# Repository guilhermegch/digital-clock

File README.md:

# Digital clock #

This is a crystal based clock is made using only common ICs: 
- Binary Counter (CD4020, CD4017, 74HC393)
- AND gates (74HC08)
- NAND gates (CD4093)
- Multiplexer (74HC251)
- 7 segments display decoder (CD4511)

## How it works ##

This clock source is on a 32.768 kHz crystal. The signal is amplified by the NAND gates and sent to a frequency divider. Since 32786 = 2^15, we use the CD4020 14 stages with the output cascaded to a CD4017, so we have a stable 1 Hz oscillator. 

The 2048 Hz (Q3) and the 64 Hz (Q8) clocks are used by the fast and slow clock adjusts. Send the three signals into a multiplexer, and the clock signal goes to the 74HC393 counter that, combined with AND gates, makes the logic circuit. 

In the end, the counter stage numbers feed a binary to seven segment display decoder.

The seconds are counted in binary by the LEDs. Above the displays is the decimal. The displays show the hours in the 24h format, the Brazilian standard.

The PCB size is 100 x 100 mm, to feat on the promotional range of Chinese manufactures, like [PCBWay](https://www.pcbway.com) and [JLCPCB](https://jlcpcb.com).

Feel free to change the project to meet your needs.

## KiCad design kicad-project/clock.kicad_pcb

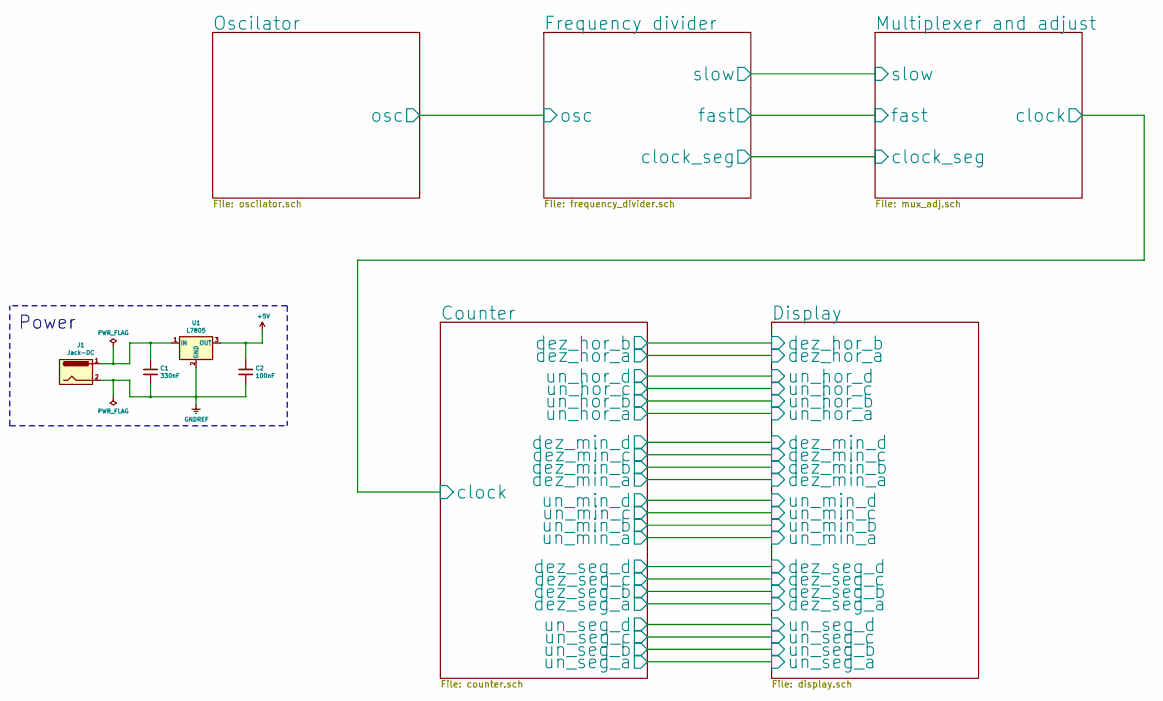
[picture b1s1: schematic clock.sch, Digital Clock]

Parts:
C1: 330nF; C_Rect_L7.0mm_W2.5mm_P5.00mm
C2: 100nF; C_Disc_D9.0mm_W5.0mm_P7.50mm
J1: Jack-DC; BarrelJack_Horizontal
U1: L7805; TO-220-3_Vertical

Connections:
+5V: C2.1, U1.3 (OUT); also elsewhere on the board
GNDREF: C1.2, C2.2, J1.2, U1.2 (GND); also elsewhere on the board
unnamed: C1.1, J1.1, U1.1 (IN)

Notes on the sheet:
Power

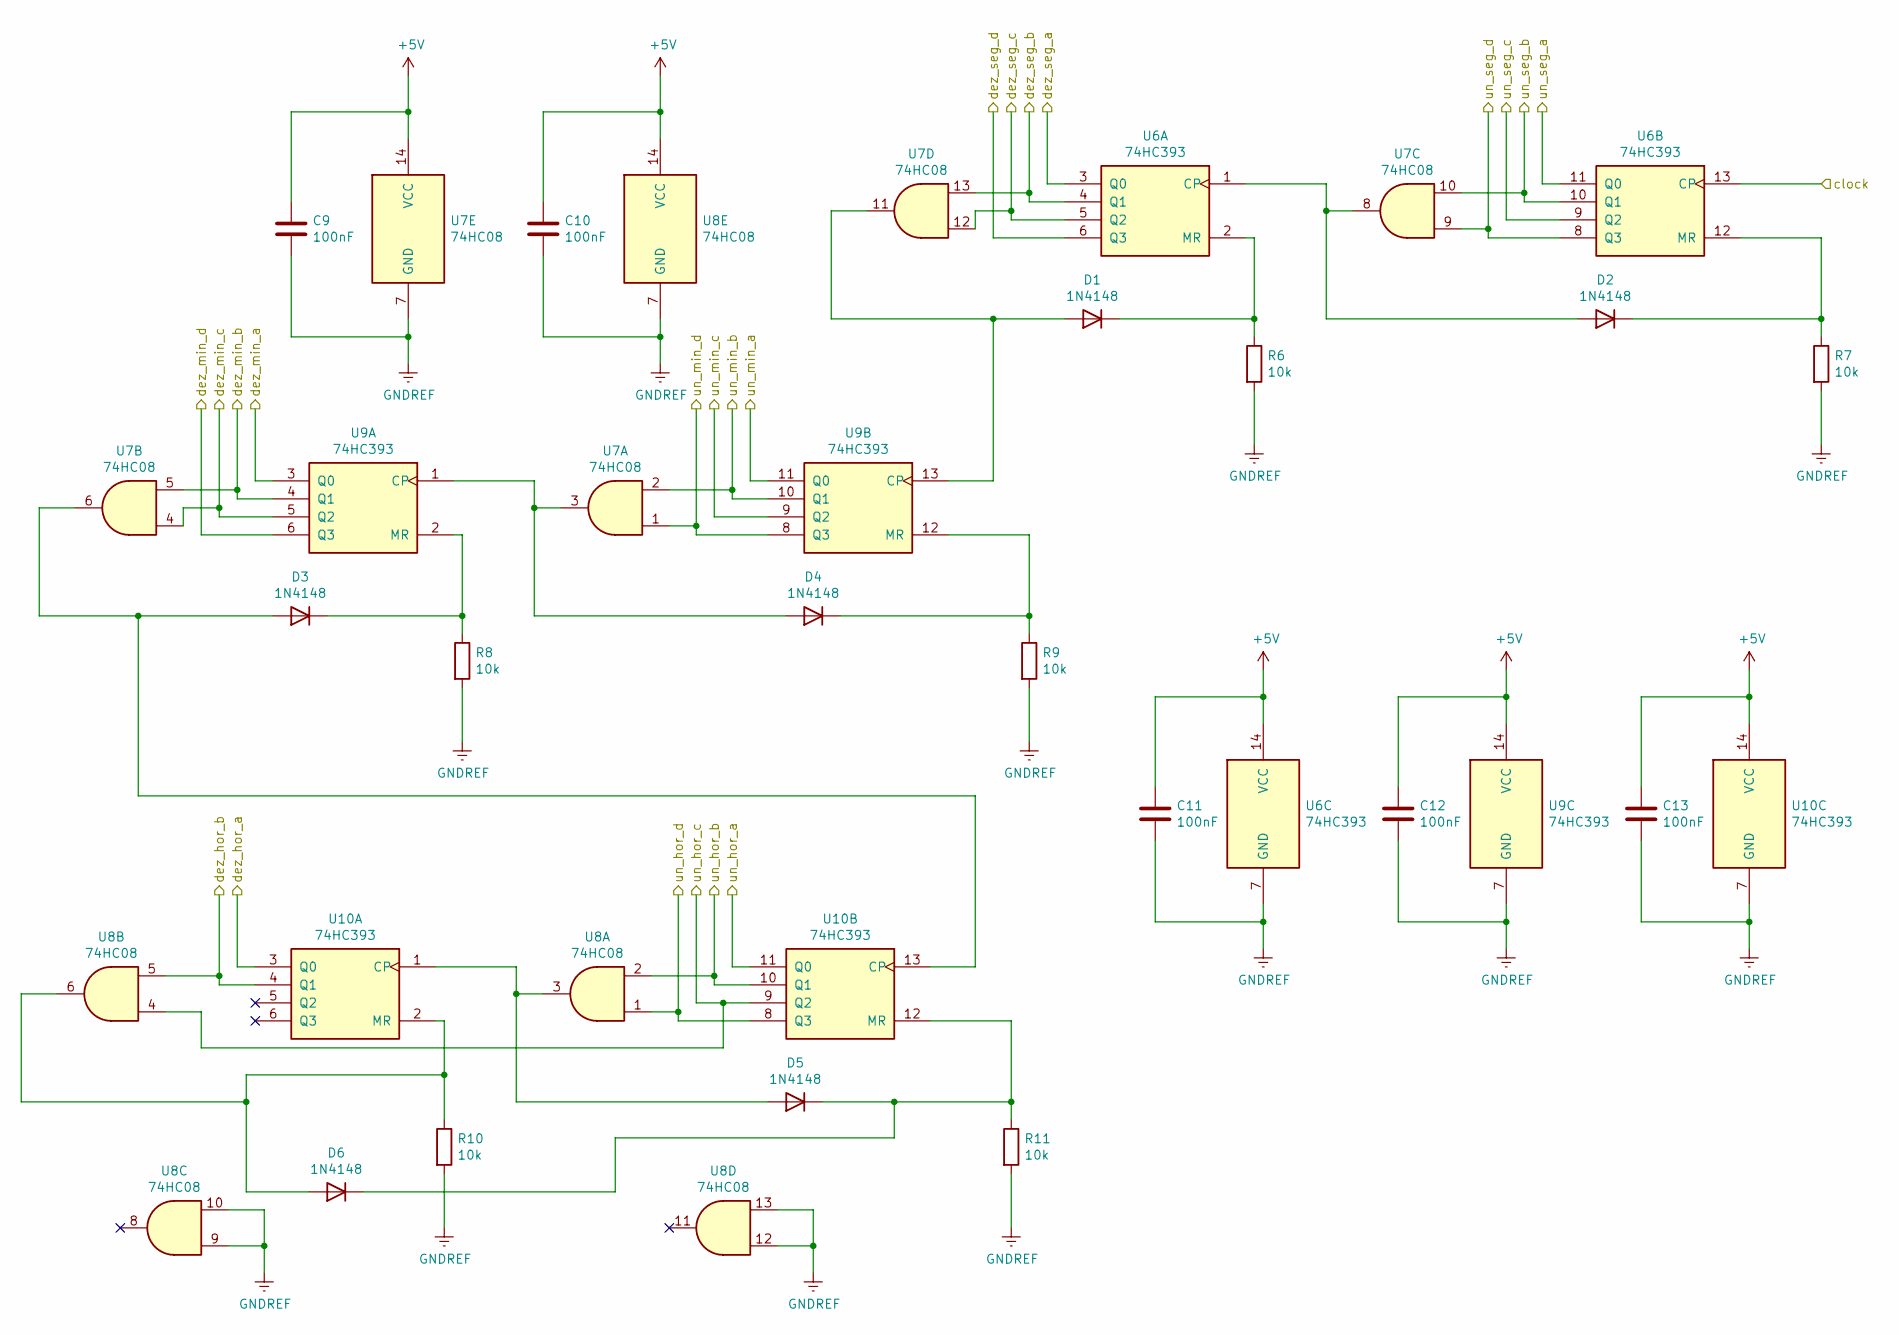
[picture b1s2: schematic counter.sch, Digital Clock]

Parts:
C9, C10, C11, C12, C13: 100nF; C_Disc_D9.0mm_W5.0mm_P7.50mm
D1, D2, D3, D4, D5, D6: 1N4148; D_DO-35_SOD27_P7.62mm_Horizontal
R6, R7, R8, R9, R10, R11: 10k; R_Axial_DIN0204_L3.6mm_D1.6mm_P7.62mm_Horizontal
U6, U9, U10: 74HC393; DIP-14_W7.62mm_Socket_LongPads
U7, U8: 74HC08; DIP-14_W7.62mm_Socket_LongPads

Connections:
+5V: C9.1, C10.1, C11.1, C12.1, C13.1, U6.14 (VCC), U7.14 (VCC), U8.14 (VCC), U9.14 (VCC), U10.14 (VCC); also elsewhere on the board
/Contador/clock: U6.13 (CP); also elsewhere on the board
/Contador/dez_hor_a: U10.3 (Q0); also elsewhere on the board
/Contador/dez_hor_b: U8.5, U10.4 (Q1); also elsewhere on the board
/Contador/dez_min_a: U9.3 (Q0); also elsewhere on the board
/Contador/dez_min_b: U7.5, U9.4 (Q1); also elsewhere on the board
/Contador/dez_min_c: U7.4, U9.5 (Q2); also elsewhere on the board
/Contador/dez_min_d: U9.6 (Q3); also elsewhere on the board
/Contador/dez_seg_a: U6.3 (Q0); also elsewhere on the board
/Contador/dez_seg_b: U6.4 (Q1), U7.13; also elsewhere on the board
/Contador/dez_seg_c: U6.5 (Q2), U7.12; also elsewhere on the board
/Contador/dez_seg_d: U6.6 (Q3); also elsewhere on the board
/Contador/un_hor_a: U10.11 (Q0); also elsewhere on the board
/Contador/un_hor_b: U8.2, U10.10 (Q1); also elsewhere on the board
/Contador/un_hor_c: U8.4, U10.9 (Q2); also elsewhere on the board
/Contador/un_hor_d: U8.1, U10.8 (Q3); also elsewhere on the board
/Contador/un_min_a: U9.11 (Q0); also elsewhere on the board
/Contador/un_min_b: U7.2, U9.10 (Q1); also elsewhere on the board
/Contador/un_min_c: U9.9 (Q2); also elsewhere on the board
/Contador/un_min_d: U7.1, U9.8 (Q3); also elsewhere on the board
/Contador/un_seg_a: U6.11 (Q0); also elsewhere on the board
/Contador/un_seg_b: U6.10 (Q1), U7.10; also elsewhere on the board
/Contador/un_seg_c: U6.9 (Q2); also elsewhere on the board
/Contador/un_seg_d: U6.8 (Q3), U7.9; also elsewhere on the board
GNDREF: C9.2, C10.2, C11.2, C12.2, C13.2, R6.2, R7.2, R8.2, R9.2, R10.2, R11.2, U6.7 (GND), U7.7 (GND), U8.7 (GND), U8.9, U8.10, U8.12, U8.13, U9.7 (GND), U10.7 (GND); also elsewhere on the board
unnamed: D1.1 (K), R6.1, U6.2 (MR)
unnamed: D1.2 (A), U7.11, U9.13 (CP)
unnamed: D2.1 (K), R7.1, U6.12 (MR)
unnamed: D2.2 (A), U6.1 (CP), U7.8
unnamed: D3.1 (K), R8.1, U9.2 (MR)
unnamed: D3.2 (A), U7.6, U10.13 (CP)
unnamed: D4.1 (K), R9.1, U9.12 (MR)
unnamed: D4.2 (A), U7.3, U9.1 (CP)
unnamed: D5.1 (K), D6.1 (K), R11.1, U10.12 (MR)
unnamed: D5.2 (A), U8.3, U10.1 (CP)
unnamed: D6.2 (A), R10.1, U8.6, U10.2 (MR)

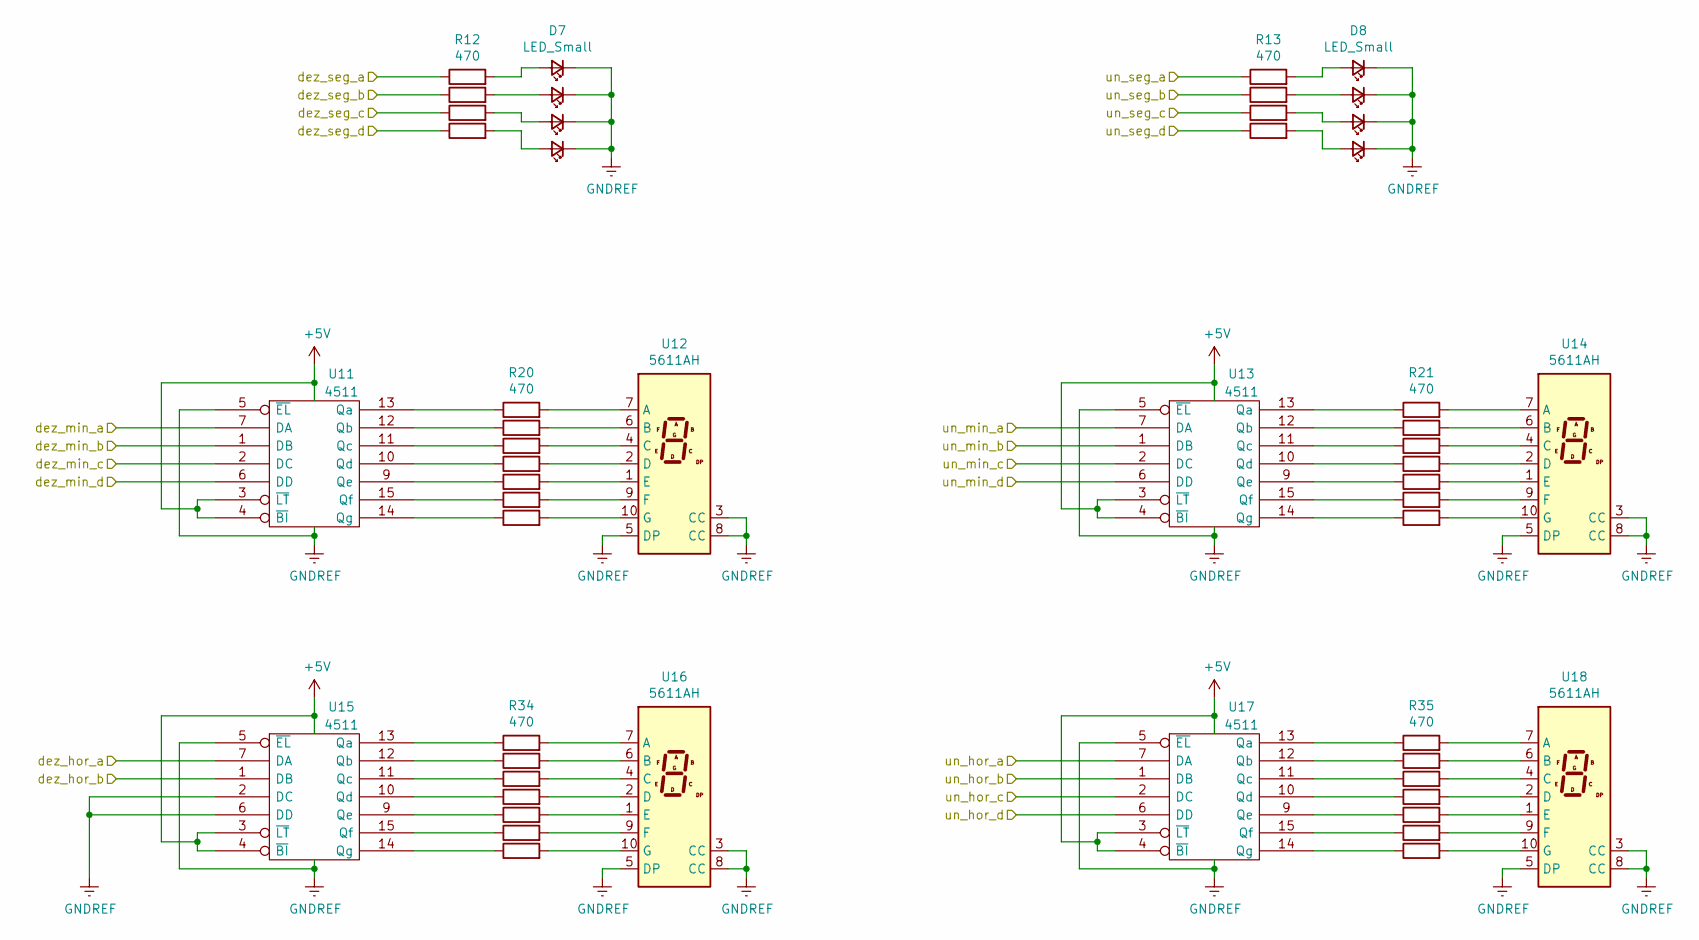
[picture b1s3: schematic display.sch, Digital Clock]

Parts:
D7, D8, D9, D10, D11, D12, D13, D14: LED_Small; LED_D5.0mm
R12, R13, R14, R15, R16, R17, R18, R19, R20, R21, R22, R23, R24, R25, R26, R27, R28, R29, R30, R31, R32, R33, R34, R35, R36, R37, R38, R39, R40, R41, R42, R43, R44, R45, R46, R47: 470; R_Axial_DIN0204_L3.6mm_D1.6mm_P7.62mm_Horizontal
U11, U13, U15, U17: 4511; DIP-16_W7.62mm_Socket_LongPads
U12, U14, U16, U18: 5611AH; D1X8K

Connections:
+5V: U11.3 (~LT), U11.4 (~BI), U11.16 (Vdd), U13.3 (~LT), U13.4 (~BI), U13.16 (Vdd), U15.3 (~LT), U15.4 (~BI), U15.16 (Vdd), U17.3 (~LT), U17.4 (~BI), U17.16 (Vdd); also elsewhere on the board
/Contador/dez_hor_a: U15.7 (DA); also elsewhere on the board
/Contador/dez_hor_b: U15.1 (DB); also elsewhere on the board
/Contador/dez_min_a: U11.7 (DA); also elsewhere on the board
/Contador/dez_min_b: U11.1 (DB); also elsewhere on the board
/Contador/dez_min_c: U11.2 (DC); also elsewhere on the board
/Contador/dez_min_d: U11.6 (DD); also elsewhere on the board
/Contador/dez_seg_a: R12.1; also elsewhere on the board
/Contador/dez_seg_b: R14.1; also elsewhere on the board
/Contador/dez_seg_c: R16.1; also elsewhere on the board
/Contador/dez_seg_d: R18.1; also elsewhere on the board
/Contador/un_hor_a: U17.7 (DA); also elsewhere on the board
/Contador/un_hor_b: U17.1 (DB); also elsewhere on the board
/Contador/un_hor_c: U17.2 (DC); also elsewhere on the board
/Contador/un_hor_d: U17.6 (DD); also elsewhere on the board
/Contador/un_min_a: U13.7 (DA); also elsewhere on the board
/Contador/un_min_b: U13.1 (DB); also elsewhere on the board
/Contador/un_min_c: U13.2 (DC); also elsewhere on the board
/Contador/un_min_d: U13.6 (DD); also elsewhere on the board
/Contador/un_seg_a: R13.1; also elsewhere on the board
/Contador/un_seg_b: R15.1; also elsewhere on the board
/Contador/un_seg_c: R17.1; also elsewhere on the board
/Contador/un_seg_d: R19.1; also elsewhere on the board
GNDREF: D7.1 (K), D8.1 (K), D9.1 (K), D10.1 (K), D11.1 (K), D12.1 (K), D13.1 (K), D14.1 (K), U11.5 (~EL), U11.8 (Vss), U12.3 (CC), U12.5 (DP), U12.8 (CC), U13.5 (~EL), U13.8 (Vss), U14.3 (CC), U14.5 (DP), U14.8 (CC), U15.2 (DC), U15.5 (~EL), U15.6 (DD), U15.8 (Vss), U16.3 (CC), U16.5 (DP), U16.8 (CC), U17.5 (~EL), U17.8 (Vss), U18.3 (CC), U18.5 (DP), U18.8 (CC); also elsewhere on the board
unnamed: D7.2 (A), R12.2
unnamed: D8.2 (A), R13.2
unnamed: D9.2 (A), R14.2
unnamed: D10.2 (A), R15.2
unnamed: D11.2 (A), R16.2
unnamed: D12.2 (A), R17.2
unnamed: D13.2 (A), R18.2
unnamed: D14.2 (A), R19.2
unnamed: R20.1, U11.13 (Qa)
unnamed: R20.2, U12.7 (A)
unnamed: R21.1, U13.13 (Qa)
unnamed: R21.2, U14.7 (A)
unnamed: R22.1, U11.12 (Qb)
unnamed: R22.2, U12.6 (B)
unnamed: R23.1, U13.12 (Qb)
unnamed: R23.2, U14.6 (B)
unnamed: R24.1, U11.11 (Qc)
unnamed: R24.2, U12.4 (C)
unnamed: R25.1, U13.11 (Qc)
unnamed: R25.2, U14.4 (C)
unnamed: R26.1, U11.10 (Qd)
unnamed: R26.2, U12.2 (D)
unnamed: R27.1, U13.10 (Qd)
unnamed: R27.2, U14.2 (D)
unnamed: R28.1, U11.9 (Qe)
unnamed: R28.2, U12.1 (E)
unnamed: R29.1, U13.9 (Qe)
unnamed: R29.2, U14.1 (E)
unnamed: R30.1, U11.15 (Qf)
unnamed: R30.2, U12.9 (F)
unnamed: R31.1, U13.15 (Qf)
unnamed: R31.2, U14.9 (F)
unnamed: R32.1, U11.14 (Qg)
unnamed: R32.2, U12.10 (G)
unnamed: R33.1, U13.14 (Qg)
unnamed: R33.2, U14.10 (G)
unnamed: R34.1, U15.13 (Qa)
unnamed: R34.2, U16.7 (A)
unnamed: R35.1, U17.13 (Qa)
unnamed: R35.2, U18.7 (A)
unnamed: R36.1, U15.12 (Qb)
unnamed: R36.2, U16.6 (B)
unnamed: R37.1, U17.12 (Qb)
unnamed: R37.2, U18.6 (B)
unnamed: R38.1, U15.11 (Qc)
unnamed: R38.2, U16.4 (C)
unnamed: R39.1, U17.11 (Qc)
unnamed: R39.2, U18.4 (C)
unnamed: R40.1, U15.10 (Qd)
unnamed: R40.2, U16.2 (D)
unnamed: R41.1, U17.10 (Qd)
unnamed: R41.2, U18.2 (D)
unnamed: R42.1, U15.9 (Qe)
unnamed: R42.2, U16.1 (E)
unnamed: R43.1, U17.9 (Qe)
unnamed: R43.2, U18.1 (E)
unnamed: R44.1, U15.15 (Qf)
unnamed: R44.2, U16.9 (F)
unnamed: R45.1, U17.15 (Qf)
unnamed: R45.2, U18.9 (F)
unnamed: R46.1, U15.14 (Qg)
unnamed: R46.2, U16.10 (G)
unnamed: R47.1, U17.14 (Qg)
unnamed: R47.2, U18.10 (G)

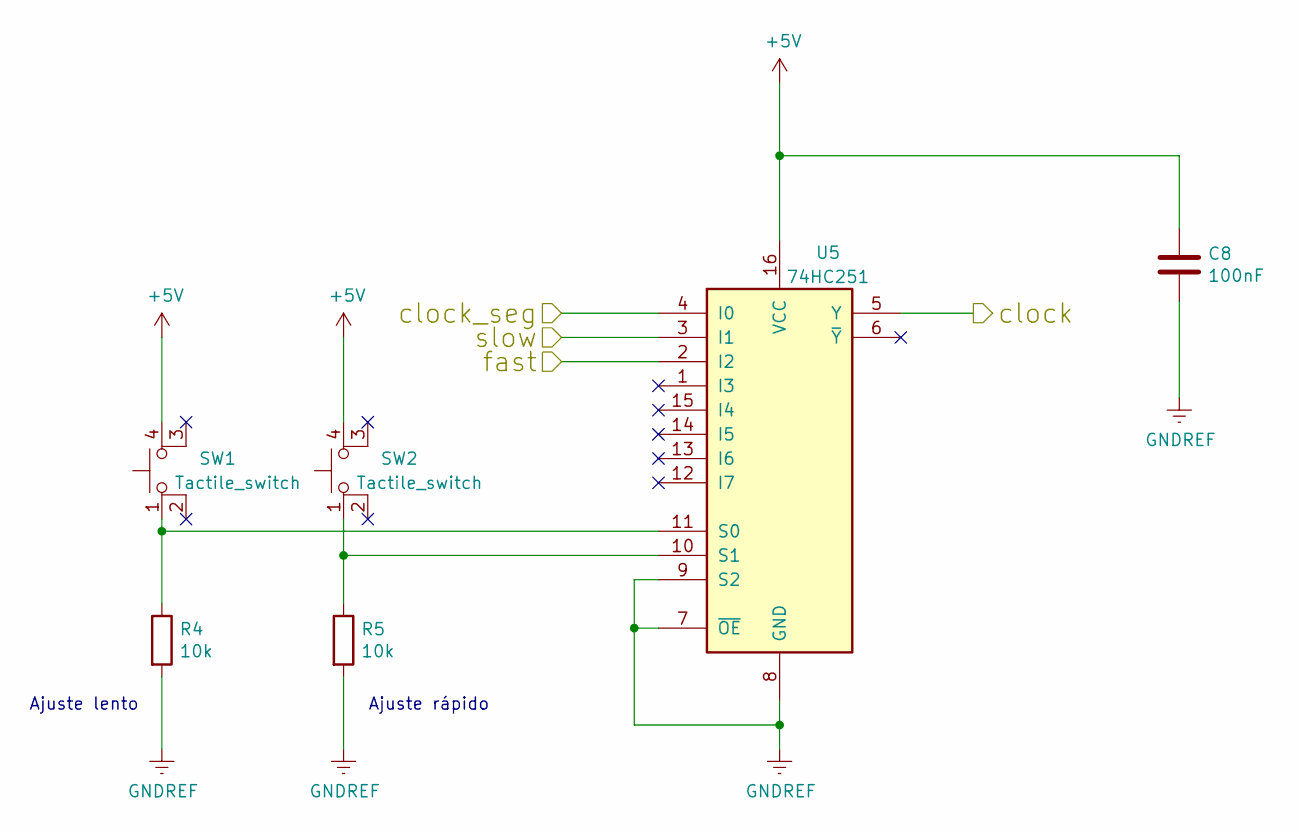
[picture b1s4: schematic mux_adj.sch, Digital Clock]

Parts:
C8: 100nF; C_Disc_D9.0mm_W5.0mm_P7.50mm
R4, R5: 10k; R_Axial_DIN0204_L3.6mm_D1.6mm_P7.62mm_Horizontal
SW1, SW2: Tactile_switch; SW_PUSH_6mm_H5mm
U5: 74HC251; DIP-16_W7.62mm_Socket_LongPads

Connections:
+5V: C8.1, SW1.4 (A), SW2.4 (A), U5.16 (VCC); also elsewhere on the board
/Contador/clock: U5.5 (Y); also elsewhere on the board
/Divisor de frequência/clock_seg: U5.4 (I0); also elsewhere on the board
/Divisor de frequência/fast: U5.2 (I2); also elsewhere on the board
/Divisor de frequência/slow: U5.3 (I1); also elsewhere on the board
GNDREF: C8.2, R4.2, R5.2, U5.7 (~OE), U5.8 (GND), U5.9 (S2); also elsewhere on the board
unnamed: R4.1, SW1.1, U5.11 (S0)
unnamed: R5.1, SW2.1, U5.10 (S1)

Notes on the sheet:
Ajuste lento
Ajuste rápido

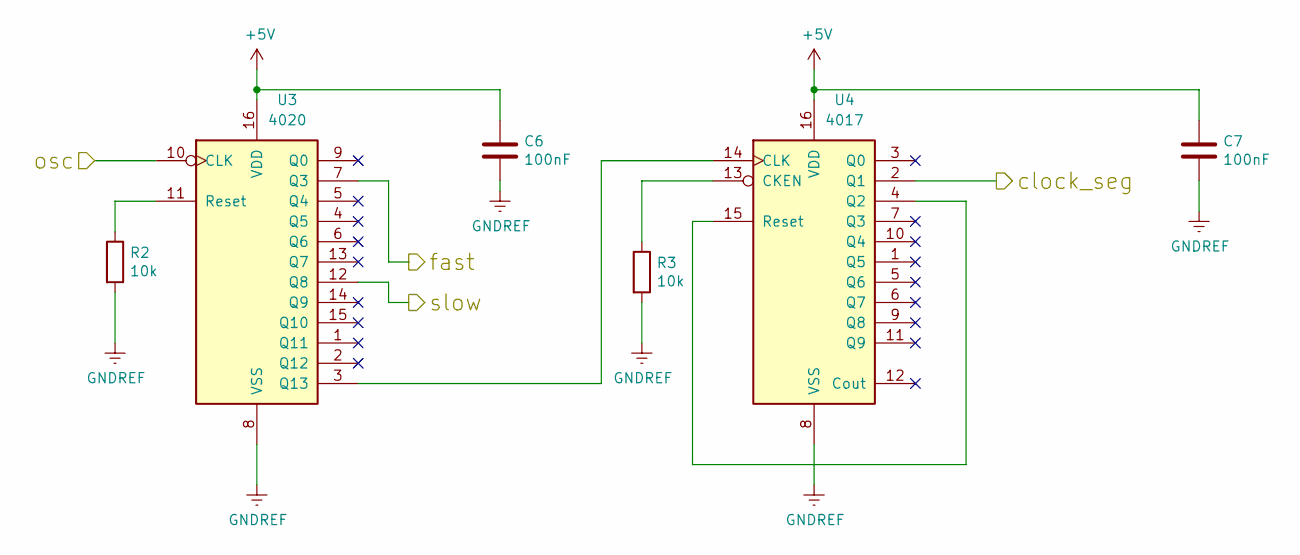
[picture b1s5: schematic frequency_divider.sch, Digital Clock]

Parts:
C6, C7: 100nF; C_Disc_D9.0mm_W5.0mm_P7.50mm
R2, R3: 10k; R_Axial_DIN0204_L3.6mm_D1.6mm_P7.62mm_Horizontal
U3: 4020; DIP-16_W7.62mm_Socket_LongPads
U4: 4017; DIP-16_W7.62mm_Socket_LongPads

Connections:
+5V: C6.1, C7.1, U3.16 (VDD), U4.16 (VDD); also elsewhere on the board
/Divisor de frequência/clock_seg: U4.2 (Q1); also elsewhere on the board
/Divisor de frequência/fast: U3.7 (Q3); also elsewhere on the board
/Divisor de frequência/osc: U3.10 (CLK); also elsewhere on the board
/Divisor de frequência/slow: U3.12 (Q8); also elsewhere on the board
GNDREF: C6.2, C7.2, R2.2, R3.2, U3.8 (VSS), U4.8 (VSS); also elsewhere on the board
unnamed: R2.1, U3.11 (Reset)
unnamed: R3.1, U4.13 (CKEN)
unnamed: U3.3 (Q13), U4.14 (CLK)
unnamed: U4.4 (Q2), U4.15 (Reset)

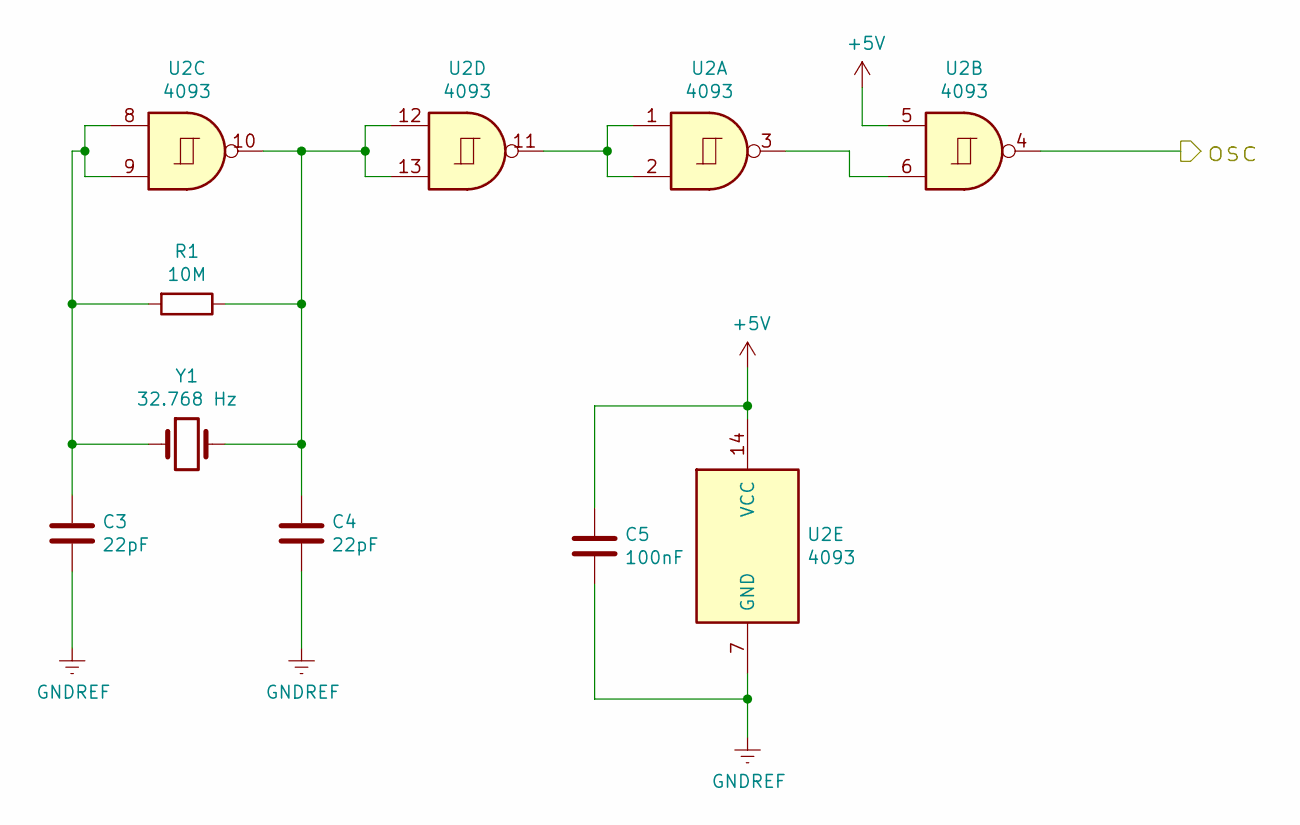
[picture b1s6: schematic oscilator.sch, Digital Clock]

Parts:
C3, C4: 22pF; C_Disc_D3.0mm_W2.0mm_P2.50mm
C5: 100nF; C_Disc_D9.0mm_W5.0mm_P7.50mm
R1: 10M; R_Axial_DIN0204_L3.6mm_D1.6mm_P7.62mm_Horizontal
U2: 4093; DIP-14_W7.62mm_Socket_LongPads
Y1: 32.768 Hz; Crystal_Round_D3.0mm_Vertical

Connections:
+5V: C5.1, U2.5, U2.14 (VCC); also elsewhere on the board
/Divisor de frequência/osc: U2.4; also elsewhere on the board
GNDREF: C3.2, C4.2, C5.2, U2.7 (GND); also elsewhere on the board
unnamed: C3.1, R1.2, U2.8, U2.9, Y1.1
unnamed: C4.1, R1.1, U2.10, U2.12, U2.13, Y1.2
unnamed: U2.1, U2.2, U2.11
unnamed: U2.3, U2.6

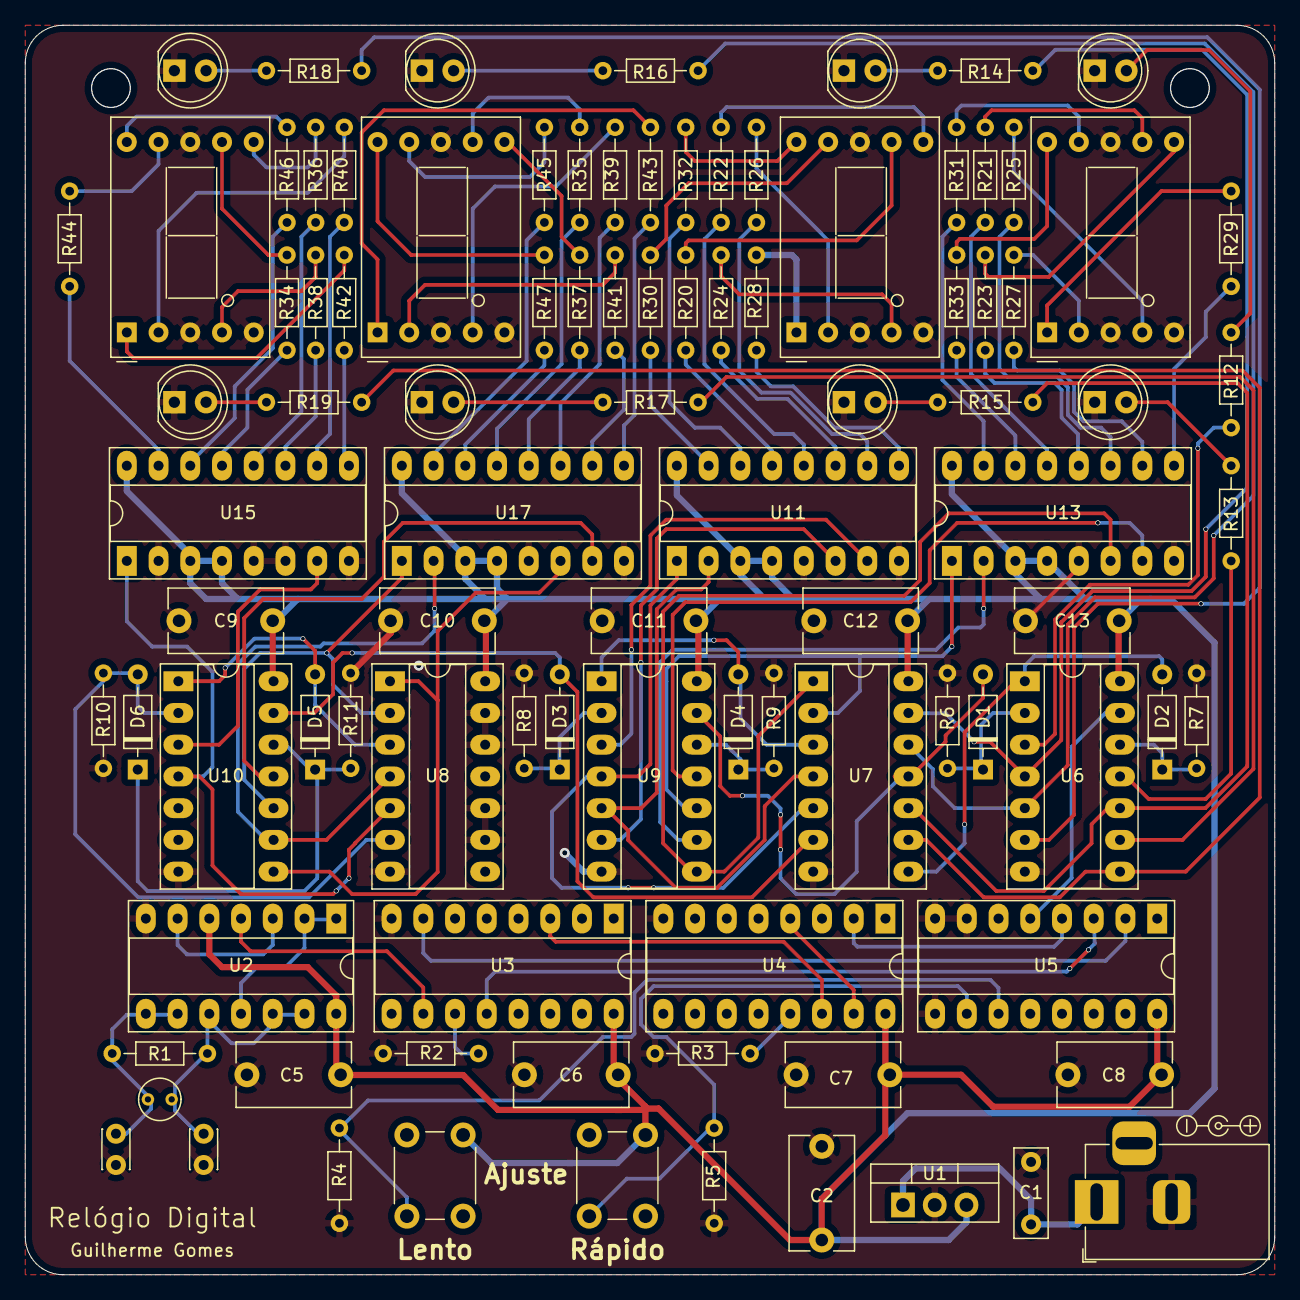
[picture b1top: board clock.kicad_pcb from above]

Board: 2 copper layers, 100.0 x 100.0 mm, 96 parts (0 on the bottom side), 115 nets.

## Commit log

2021-06-24 Adding readme to the project
2021-06-24 Adding BOM list
2021-06-24 Adding the project schematic
2021-06-24 Adding the KiCAD project
2021-06-24 Adding the components datasheets
2021-06-24 Adding the Gerber files
